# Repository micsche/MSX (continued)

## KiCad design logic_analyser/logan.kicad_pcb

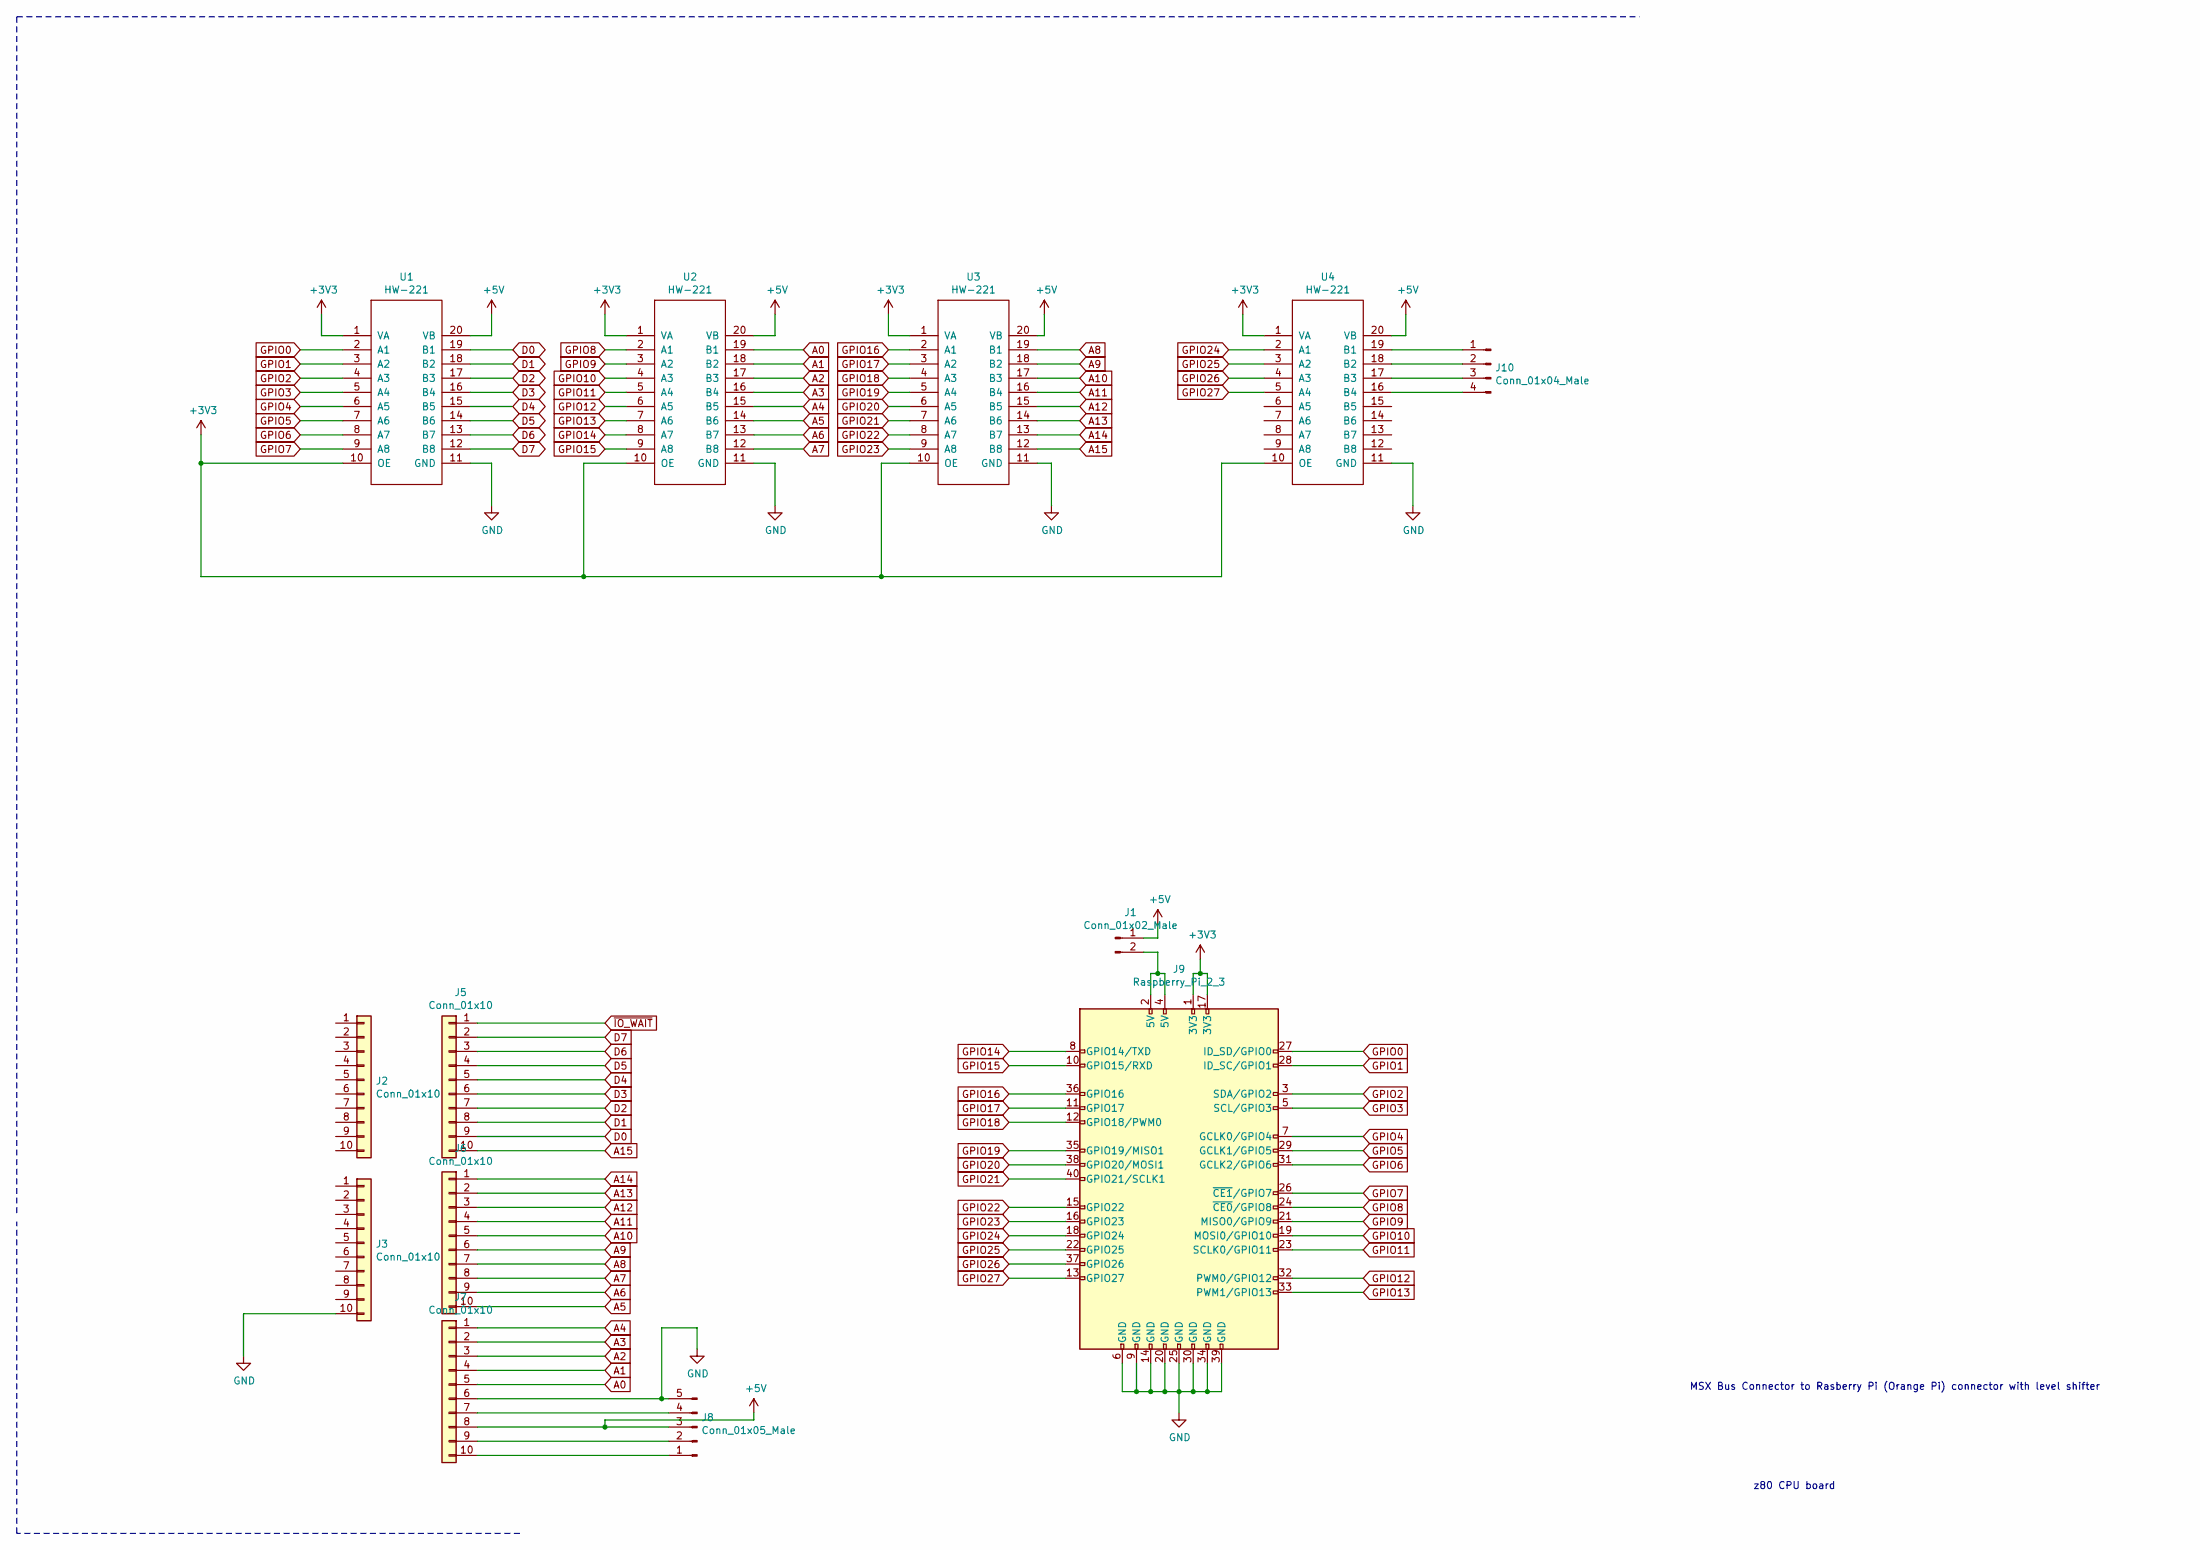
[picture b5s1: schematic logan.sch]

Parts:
J1: Conn_01x02_Male; PinHeader_1x02_P2.54mm_Vertical
J2, J3, J5, J6, J7: Conn_01x10; PinHeader_1x10_P2.54mm_Vertical
J8: Conn_01x05_Male; PinHeader_1x05_P2.54mm_Vertical
J9: Raspberry_Pi_2_3; PinHeader_2x20_P2.54mm_Vertical
J10: Conn_01x04_Male; PinHeader_1x04_P2.54mm_Vertical
U1, U2, U3, U4: HW-221; hw-221_breakout

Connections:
+3V3: J9.1 (3V3), J9.17 (3V3), U1.1 (VA), U1.10 (OE), U2.1 (VA), U2.10 (OE), U3.1 (VA), U3.10 (OE), U4.1 (VA), U4.10 (OE)
+5V: J1.1, J7.8, J8.3, U1.20 (VB), U2.20 (VB), U3.20 (VB), U4.20 (VB)
A0: J7.5, U2.19 (B1)
A1: J7.4, U2.18 (B2)
A2: J7.3, U2.17 (B3)
A3: J7.2, U2.16 (B4)
A4: J7.1, U2.15 (B5)
A5: J6.10, U2.14 (B6)
A6: J6.9, U2.13 (B7)
A7: J6.8, U2.12 (B8)
A8: J6.7, U3.19 (B1)
A9: J6.6, U3.18 (B2)
A10: J6.5, U3.17 (B3)
A11: J6.4, U3.16 (B4)
A12: J6.3, U3.15 (B5)
A13: J6.2, U3.14 (B6)
A14: J6.1, U3.13 (B7)
A15: J5.10, U3.12 (B8)
D0: J5.9, U1.19 (B1)
D1: J5.8, U1.18 (B2)
D2: J5.7, U1.17 (B3)
D3: J5.6, U1.16 (B4)
D4: J5.5, U1.15 (B5)
D5: J5.4, U1.14 (B6)
D6: J5.3, U1.13 (B7)
D7: J5.2, U1.12 (B8)
GND: J3.10, J7.6, J8.5, J9.6 (GND), J9.9 (GND), J9.14 (GND), J9.20 (GND), J9.25 (GND), J9.30 (GND), J9.34 (GND), J9.39 (GND), U1.11 (GND), U2.11 (GND), U3.11 (GND), U4.11 (GND)
GPIO0: J9.27 (ID_SD/GPIO0), U1.2 (A1)
GPIO1: J9.28 (ID_SC/GPIO1), U1.3 (A2)
GPIO2: J9.3 (SDA/GPIO2), U1.4 (A3)
GPIO3: J9.5 (SCL/GPIO3), U1.5 (A4)
GPIO4: J9.7 (GCLK0/GPIO4), U1.6 (A5)
GPIO5: J9.29 (GCLK1/GPIO5), U1.7 (A6)
GPIO6: J9.31 (GCLK2/GPIO6), U1.8 (A7)
GPIO7: J9.26 (~CE1~/GPIO7), U1.9 (A8)
GPIO8: J9.24 (~CE0~/GPIO8), U2.2 (A1)
GPIO9: J9.21 (MISO0/GPIO9), U2.3 (A2)
GPIO10: J9.19 (MOSI0/GPIO10), U2.4 (A3)
GPIO11: J9.23 (SCLK0/GPIO11), U2.5 (A4)
GPIO12: J9.32 (PWM0/GPIO12), U2.6 (A5)
GPIO13: J9.33 (PWM1/GPIO13), U2.7 (A6)
GPIO14: J9.8 (GPIO14/TXD), U2.8 (A7)
GPIO15: J9.10 (GPIO15/RXD), U2.9 (A8)
GPIO16: J9.36 (GPIO16), U3.2 (A1)
GPIO17: J9.11 (GPIO17), U3.3 (A2)
GPIO18: J9.12 (GPIO18/PWM0), U3.4 (A3)
GPIO19: J9.35 (GPIO19/MISO1), U3.5 (A4)
GPIO20: J9.38 (GPIO20/MOSI1), U3.6 (A5)
GPIO21: J9.40 (GPIO21/SCLK1), U3.7 (A6)
GPIO22: J9.15 (GPIO22), U3.8 (A7)
GPIO23: J9.16 (GPIO23), U3.9 (A8)
GPIO24: J9.18 (GPIO24), U4.2 (A1)
GPIO25: J9.22 (GPIO25), U4.3 (A2)
GPIO26: J9.37 (GPIO26), U4.4 (A3)
GPIO27: J9.13 (GPIO27), U4.5 (A4)
unnamed: J1.2, J9.2 (5V), J9.4 (5V)
unnamed: J7.7, J8.4
unnamed: J7.9, J8.2
unnamed: J7.10, J8.1
unnamed: J10.1, U4.19 (B1)
unnamed: J10.2, U4.18 (B2)
unnamed: J10.3, U4.17 (B3)
unnamed: J10.4, U4.16 (B4)
~IO_WAIT: J5.1

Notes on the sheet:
MSX Bus Connector to Rasberry Pi (Orange Pi) connector with level shifter
z80 CPU board

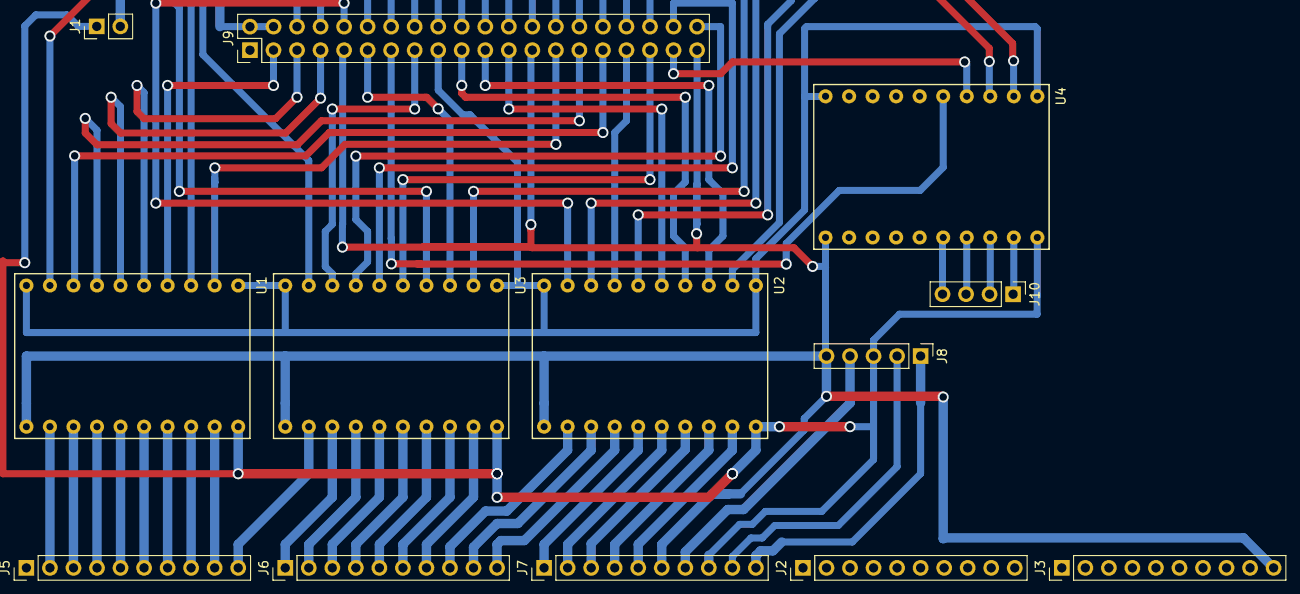
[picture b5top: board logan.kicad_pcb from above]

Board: 2 copper layers, 13 parts (0 on the bottom side), 63 nets.

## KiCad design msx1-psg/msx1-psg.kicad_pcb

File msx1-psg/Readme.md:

# MSX Sound card 
(untested)

The soundcard uses stock YM2149 (AY-3-8910 clone)
The MSX also uses this chip to interface to the joysticks. This version of the board does not include joystick ports (scope for Future Work).

The sound is fed into the BUS pin J3-8. However, the board has enough space to include a small-speaker. (scope for Future Work)

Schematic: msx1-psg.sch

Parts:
C1: 10u; CP_Radial_D5.0mm_P2.00mm
C2: 47u; CP_Radial_D5.0mm_P2.50mm
C3: 10u; CP_Radial_D5.0mm_P2.50mm
C4, C5: C; C_Rect_L7.0mm_W3.5mm_P5.00mm
J2, J3, J5, J6, J7: Conn_01x10; PinHeader_1x10_P2.54mm_Vertical
R2: 470R; R_Axial_DIN0207_L6.3mm_D2.5mm_P7.62mm_Horizontal
R3: 1.2k; R_Axial_DIN0207_L6.3mm_D2.5mm_P7.62mm_Horizontal
RV1: 10k; Potentiometer_ACP_CA14-H4_Horizontal
U7: YM2149; DIP-40_W15.24mm_LongPads
U8: 74LS02; DIP-14_W7.62mm_LongPads
U9: LM386; DIP-8_W7.62mm_LongPads

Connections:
+5V: C4.1, C5.1, J3.9, J7.8, U7.24, U7.25, U7.28, U7.40, U8.14, U9.6
A0: J7.5, U8.3
A1: J7.4, U8.11
A2: J7.3
A3: J7.2
A4: J7.1
A5: J6.10
A6: J6.9
A7: J6.8
A8: J6.7
A9: J6.6
A10: J6.5
A11: J6.4
A12: J6.3
A13: J6.2
A14: J6.1
A15: J5.10
CLK: J7.7, U7.22
D0: J5.9, U7.37
D1: J5.8, U7.36
D2: J5.7, U7.35
D3: J5.6, U7.34
D4: J5.5, U7.33
D5: J5.4, U7.32
D6: J5.3, U7.31
D7: J5.2, U7.30
GND: C2.2, C4.2, C5.2, J2.5, J3.10, J7.6, R2.2, RV1.3, U7.1, U7.26, U8.7, U9.2, U9.4
unnamed: C1.1, RV1.1
unnamed: C1.2, R2.1, U7.3, U7.4, U7.38
unnamed: C2.1, U9.7
unnamed: C3.1, U9.1
unnamed: C3.2, R3.2
unnamed: R3.1, U9.8
unnamed: RV1.2, U9.3
unnamed: U7.27, U8.13
unnamed: U7.29, U8.1
RESET: J2.2
SND: J3.8, U9.5
exp1_en: J3.2
ppi_en: J2.8
prn_en: J3.1
psg_en: J2.9, U8.2, U8.12
rtc_en: J2.7
ser_en: J3.3
vdp_en: J2.10
~INT: J7.9
~IORQ: J2.6
~IO_WAIT: J5.1
~MREQ: J2.4
~RD: J2.1
~RESET: J2.3, U7.23
~SLTSL0: J3.4
~SLTSL1: J3.5
~SLTSL2: J3.6
~SLTSL3: J3.7
~WR: J7.10

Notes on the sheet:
MSX 1 - PPI + PSG Keyboard Interface Sound Interface
Z80 CPU board + clock and reset circuitry + 16k ROM/ 64k RAM
z80 CPU board

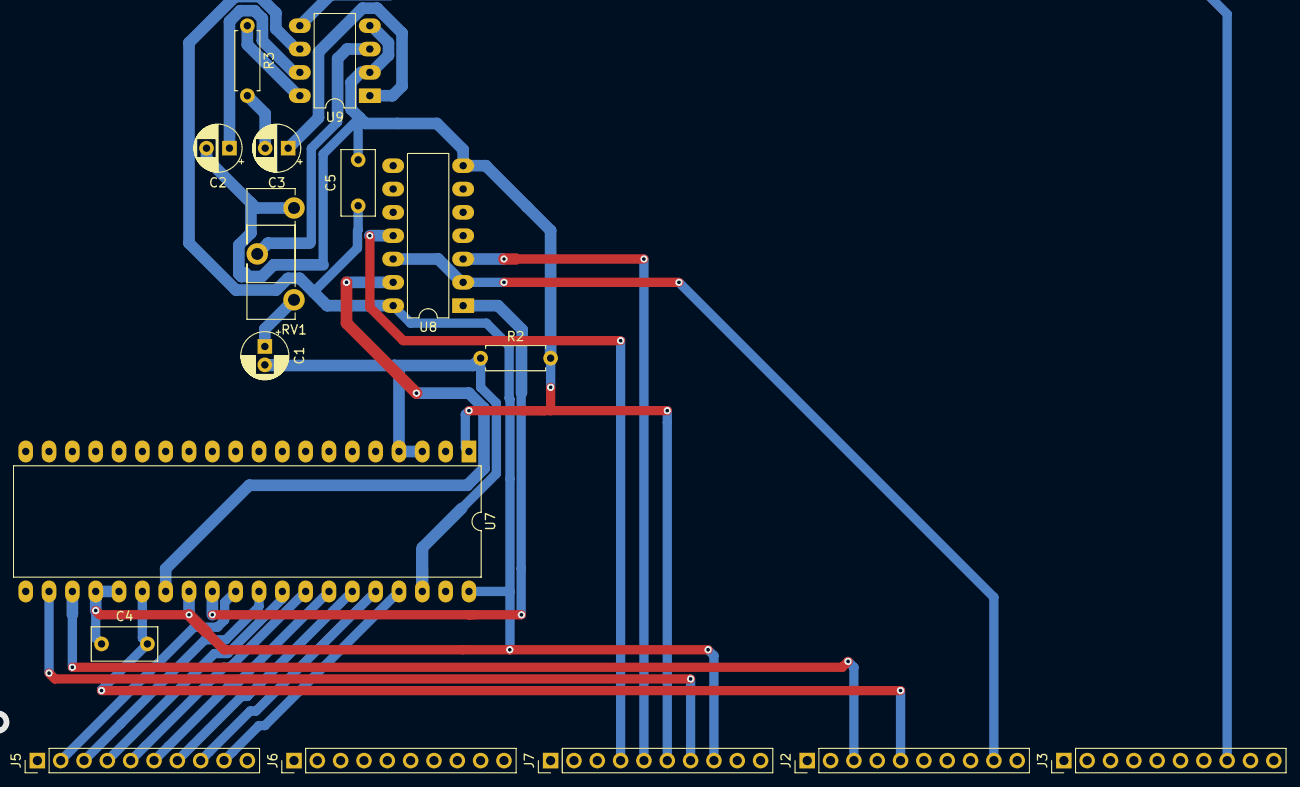
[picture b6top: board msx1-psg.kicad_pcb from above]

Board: 2 copper layers, 16 parts (0 on the bottom side), 25 nets.

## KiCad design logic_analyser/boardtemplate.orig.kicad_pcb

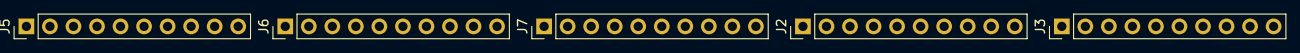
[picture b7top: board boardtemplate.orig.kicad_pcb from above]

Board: 2 copper layers, 5 parts (0 on the bottom side), 2 nets.

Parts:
J2, J3, J5, J6, J7: Conn_01x10; PinHeader_1x10_P2.54mm_Vertical

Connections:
+5V: J3.9, J7.8
GND: J2.5, J3.10, J7.6

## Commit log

2021-05-14 Upload v1
